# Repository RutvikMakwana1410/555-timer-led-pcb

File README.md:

# 555 Timer LED Blinker PCB

A **5 V LED blinker** designed in **KiCad 10**, using an **ICM7555 CMOS 555-family timer** in astable mode. The LED is designed to repeat one complete ON/OFF cycle approximately every **1.01 seconds** while power is connected.

The repository includes the schematic, routed PCB layout, 3D preview, Gerber layers and drill files.

## 3D Preview

## Component Values

| Reference | Value / component | Function |
|---|---|---|
| U1 | ICM7555; schematic value `ICM7555xB` | CMOS timer configured as an astable oscillator |
| R1 | 10 kΩ | Timing resistor between +5 V and discharge pin 7 |
| R2 | 68 kΩ | Timing resistor between pin 7 and the timing-capacitor node |
| R3 | 1 kΩ | LED current-limiting resistor |
| C1 | 100 nF | Supply decoupling between +5 V and GND |
| C2 | 10 nF | Control-pin filtering from pin 5 to GND |
| C3 | 10 µF | Timing capacitor connected to pins 2 and 6 |
| D1 | LED | Visual blink indication |
| J1 | Two-pin connector | Pin 1: +5 V; pin 2: GND |

**R1, R2 and C3 determine the blink timing.** C1 and C2 provide supply/control filtering.

## How It Works

The timer runs continuously in astable mode, without a microcontroller or firmware.

1. C3 charges through **R1 + R2**. The output at pin 3 is HIGH, so current flows through R3 and D1 and the LED turns ON.
2. When C3 reaches approximately **2/3 of the supply voltage**, the output goes LOW and the internal discharge transistor turns on.
3. C3 discharges through **R2**, with the LED OFF.
4. When C3 falls to approximately **1/3 of the supply voltage**, the output goes HIGH again and the cycle repeats.

At a 5 V supply, the nominal capacitor switching levels are approximately **1.67 V** and **3.33 V**. Reset pin 4 is tied HIGH to enable normal operation.

## Calculated Blink Timing

These are **nominal steady-state calculations**, using R1 = 10,000 Ω, R2 = 68,000 Ω and C3 = 0.000010 F.

### LED ON time

`t_ON = ln(2) × (R1 + R2) × C3`

`t_ON ≈ 0.693 × (10,000 + 68,000) × 0.000010 ≈ 0.541 s`

### LED OFF time

`t_OFF = ln(2) × R2 × C3`

`t_OFF ≈ 0.693 × 68,000 × 0.000010 ≈ 0.471 s`

### Period, frequency and duty cycle

`T = t_ON + t_OFF ≈ 1.012 s`

`f = 1 / T ≈ 0.988 Hz`

`Duty cycle = t_ON / T × 100 ≈ 53.4%`

| Parameter | Calculated value |
|---|---:|
| LED ON time | 0.541 s / 541 ms |
| LED OFF time | 0.471 s / 471 ms |
| Complete blink period | 1.012 s |
| Blink frequency | 0.988 Hz, approximately 1 blink per second |
| ON duty cycle | 53.4% |

The repeating pattern is approximately **ON for 0.54 s → OFF for 0.47 s → repeat**. There is no fixed total blinking duration; the oscillator continues while the 5 V supply is applied.

**Startup:** With C3 initially discharged and an ideal sudden application of power, the first ON interval is calculated as `ln(3) × (R1 + R2) × C3 ≈ 0.857 s`. Later cycles follow the steady-state values above. Startup depends on the initial capacitor voltage and supply rise.

Actual timing will vary with resistor/capacitor tolerances, capacitor leakage and timer characteristics. The values above are calculated estimates, not measured hardware results.

Increasing C3 increases both ON and OFF times proportionally. R1 primarily sets the charging interval; R2 contributes to both charging and discharging intervals.

Timing reference: [Renesas ICM7555/ICM7556 datasheet, Figure 5 and Equations 2–3](https://www.renesas.com/en/document/dst/icm7555-icm7556-datasheet).

## Schematic

## PCB Layout

## Repository Files

| File / folder | Contents |
|---|---|
| `pcb.kicad_pro` | KiCad project settings |
| `pcb.kicad_sch` | Circuit schematic |
| `pcb.kicad_pcb` | PCB layout |
| `images/` | Schematic, PCB and 3D screenshots |
| `gerbers/555_Timer_Gerber/` | Copper, solder-mask, silkscreen and board-outline Gerbers; plated/non-plated drill files |

## Opening the Project

Download or clone this repository and open **`pcb.kicad_pro`** using **KiCad 10**. Keep the project, schematic and board files together.

## Project Status

- Schematic and PCB layout created.
- 3D preview and project images included.
- Gerber and drill files generated.
- Blink timing documented from component-value calculations.

**Designed by Rutvik.**

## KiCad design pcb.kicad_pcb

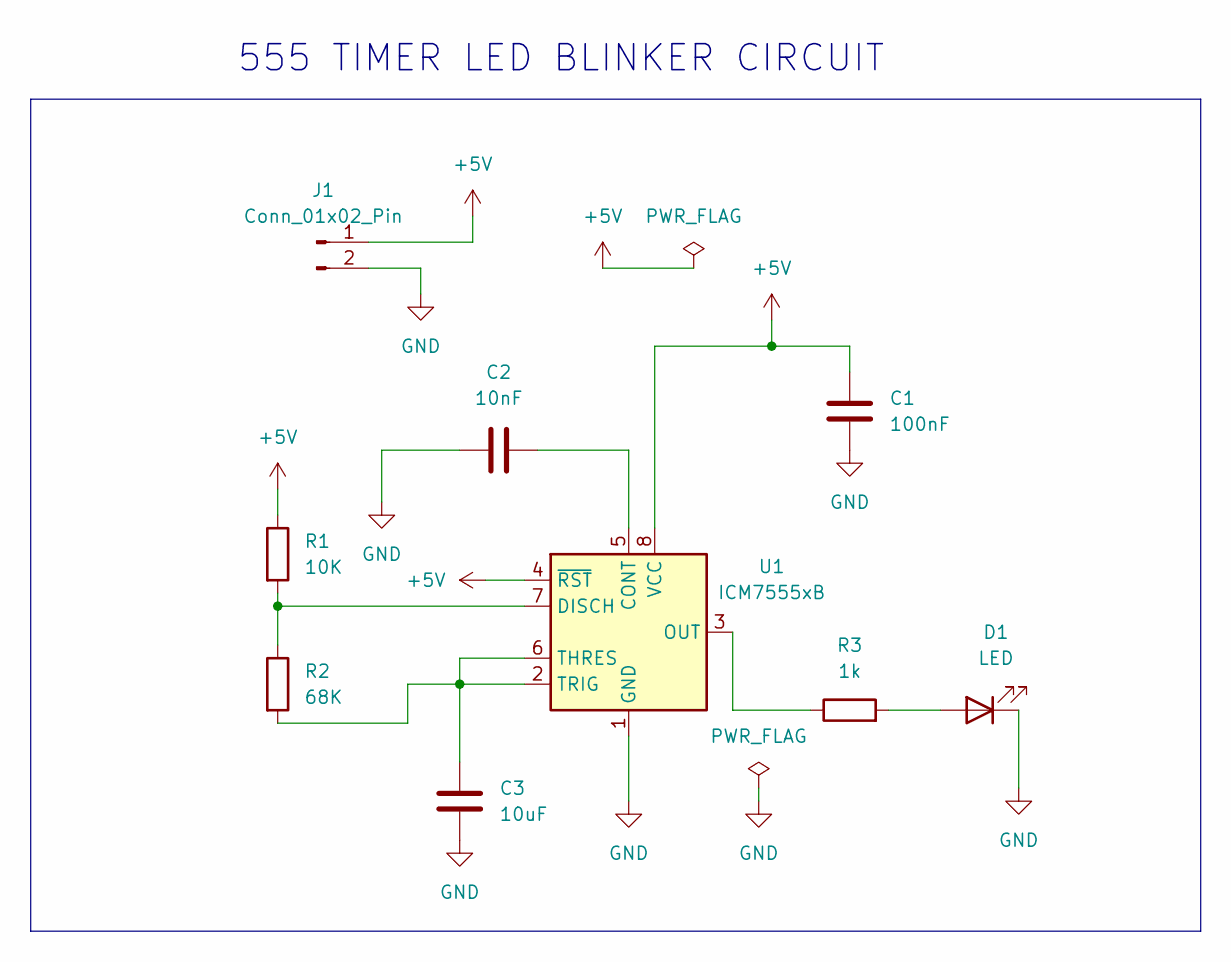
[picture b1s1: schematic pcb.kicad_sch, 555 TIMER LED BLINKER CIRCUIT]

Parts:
C1: 100nF; C_Disc_D5.1mm_W3.2mm_P5.00mm
C2: 10nF; C_Disc_D5.1mm_W3.2mm_P5.00mm
C3: 10uF; C_Radial_D5.0mm_H5.0mm_P2.00mm
D1: LED; LED_D5.0mm
J1: Conn_01x02_Pin; PinHeader_1x02_P2.54mm_Vertical
R1: 10K; R_Axial_DIN0207_L6.3mm_D2.5mm_P7.62mm_Horizontal
R2: 68K; R_Axial_DIN0207_L6.3mm_D2.5mm_P7.62mm_Horizontal
R3: 1k; R_Axial_DIN0207_L6.3mm_D2.5mm_P7.62mm_Horizontal
U1: ICM7555xB; DIP-8_W7.62mm

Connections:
+5V: C1.1, J1.1, R1.1, U1.4 (~RST), U1.8 (VCC)
GND: C1.2, C2.1, C3.2, D1.1 (K), J1.2, U1.1 (GND)
unnamed: D1.2 (A), R3.2
unnamed: C2.2, U1.5 (CONT)
unnamed: R1.2, R2.1, U1.7 (DISCH)
unnamed: R3.1, U1.3 (OUT)
unnamed: C3.1, R2.2, U1.2 (TRIG), U1.6 (THRES)

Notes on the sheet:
555 TIMER LED BLINKER CIRCUIT

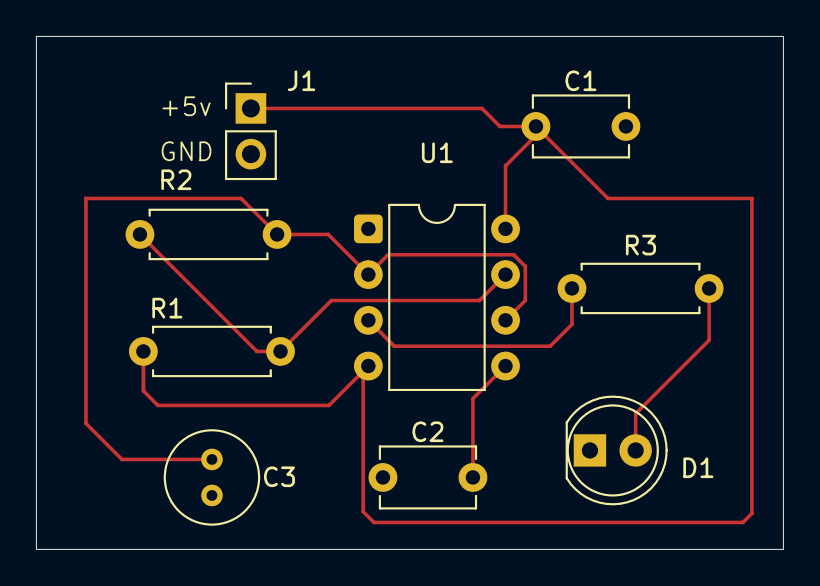
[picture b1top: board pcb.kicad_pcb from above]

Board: 2 copper layers, 41.5 x 28.5 mm, 9 parts (0 on the bottom side), 7 nets.
